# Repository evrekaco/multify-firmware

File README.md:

# multify-firmware
Sparkcore firmware resources for Multify

* Multify digital version android codes are available in digital_6wheels folder

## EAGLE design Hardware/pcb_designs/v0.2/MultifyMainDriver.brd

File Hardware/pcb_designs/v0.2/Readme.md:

Single sided version of the Multify main driver PCB.

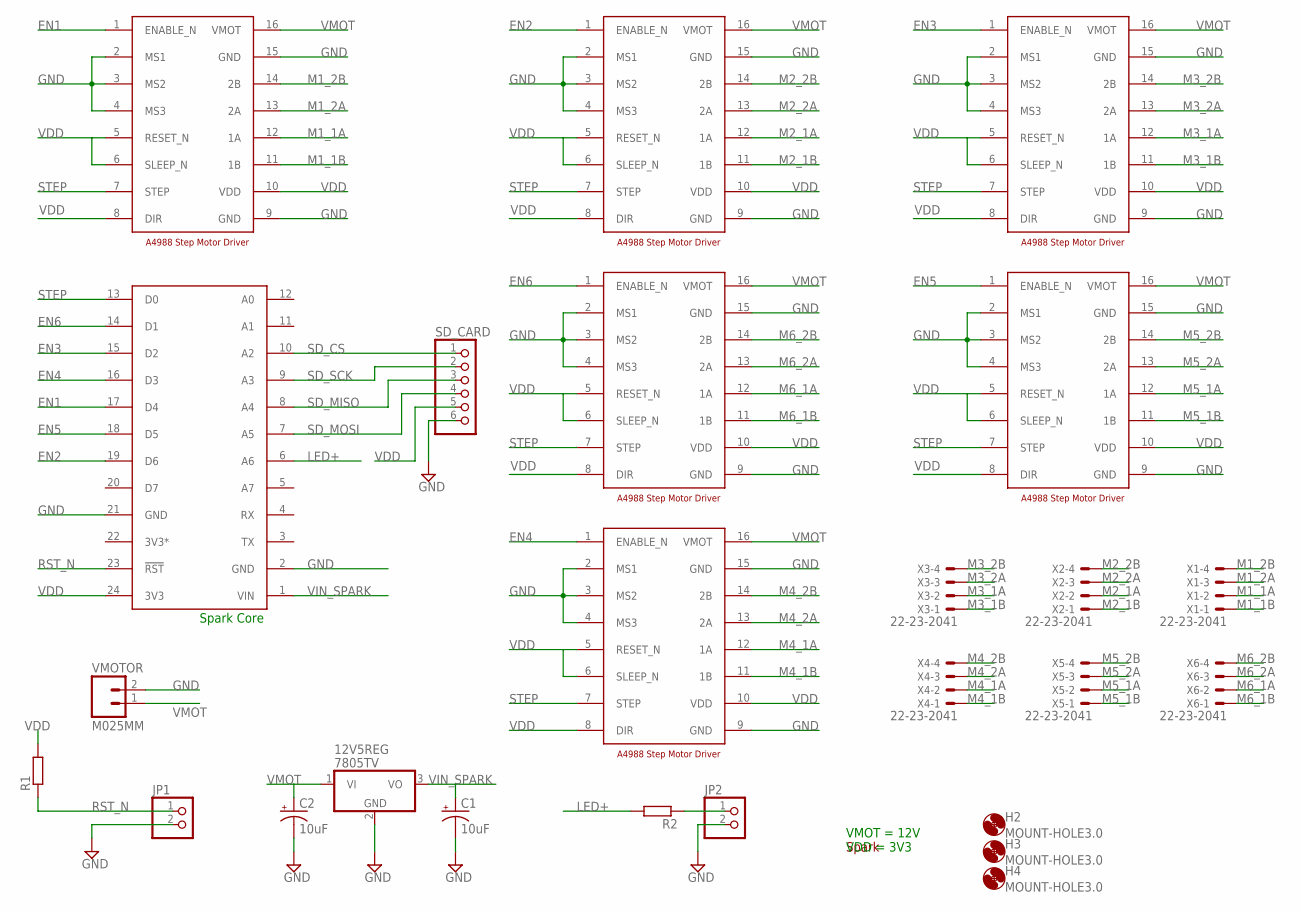
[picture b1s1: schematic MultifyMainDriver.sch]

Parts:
12V5REG: 7805TV; TO220V
C1, C2: 10uF; E3,5-8
DRIVER1, DRIVER2, DRIVER3, DRIVER4, DRIVER5, DRIVER6: A4988_DEV; A4988_PAC
H2, H3, H4: MOUNT-HOLE3.0; 3,0
JP1, JP2: PINHD-1X2; 1X02
R1, R2: R-EU_0207/7; 0207/7
SD_CARD: PINHD-1X6; 1X06
SPARK: SPARK_CORECORE; SPARK_CORE
U$2: SPARK_LOGO_WITH_PLANE; SPARK_LOGO_PLUS_PLANE
VMOTOR: M025MM; SCREWTERMINAL-5MM-2
X1, X2, X3, X4, X5, X6: 22-23-2041

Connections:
3V3*: SPARK.22 (3V3*)
EN1: DRIVER1.1 (ENABLE_N), SPARK.17 (D4)
EN2: DRIVER2.1 (ENABLE_N), SPARK.19 (D6)
EN3: DRIVER3.1 (ENABLE_N), SPARK.15 (D2)
EN4: DRIVER4.1 (ENABLE_N), SPARK.16 (D3)
EN5: DRIVER6.1 (ENABLE_N), SPARK.18 (D5)
EN6: DRIVER5.1 (ENABLE_N), SPARK.14 (D1)
GND: 12V5REG.2 (GND), C1.-, C2.-, DRIVER1.2 (MS1), DRIVER1.3 (MS2), DRIVER1.4 (MS3), DRIVER1.9 (GND), DRIVER1.15 (GND), DRIVER2.2 (MS1), DRIVER2.3 (MS2), DRIVER2.4 (MS3), DRIVER2.9 (GND), DRIVER2.15 (GND), DRIVER3.2 (MS1), DRIVER3.3 (MS2), DRIVER3.4 (MS3), DRIVER3.9 (GND), DRIVER3.15 (GND), DRIVER4.2 (MS1), DRIVER4.3 (MS2), DRIVER4.4 (MS3), DRIVER4.9 (GND), DRIVER4.15 (GND), DRIVER5.2 (MS1), DRIVER5.3 (MS2), DRIVER5.4 (MS3), DRIVER5.9 (GND), DRIVER5.15 (GND), DRIVER6.2 (MS1), DRIVER6.3 (MS2), DRIVER6.4 (MS3), DRIVER6.9 (GND), DRIVER6.15 (GND), JP1.2, JP2.2, SD_CARD.6, SPARK.2 (GND), SPARK.21 (GND), VMOTOR.2
LED+: R2.2, SPARK.6 (A6)
M1_1A: DRIVER1.12 (1A), X1.2
M1_1B: DRIVER1.11 (1B), X1.1
M1_2A: DRIVER1.13 (2A), X1.3
M1_2B: DRIVER1.14 (2B), X1.4
M2_1A: DRIVER2.12 (1A), X2.2
M2_1B: DRIVER2.11 (1B), X2.1
M2_2A: DRIVER2.13 (2A), X2.3
M2_2B: DRIVER2.14 (2B), X2.4
M3_1A: DRIVER3.12 (1A), X3.2
M3_1B: DRIVER3.11 (1B), X3.1
M3_2A: DRIVER3.13 (2A), X3.3
M3_2B: DRIVER3.14 (2B), X3.4
M4_1A: DRIVER4.12 (1A), X4.2
M4_1B: DRIVER4.11 (1B), X4.1
M4_2A: DRIVER4.13 (2A), X4.3
M4_2B: DRIVER4.14 (2B), X4.4
M5_1A: DRIVER6.12 (1A), X5.2
M5_1B: DRIVER6.11 (1B), X5.1
M5_2A: DRIVER6.13 (2A), X5.3
M5_2B: DRIVER6.14 (2B), X5.4
M6_1A: DRIVER5.12 (1A), X6.2
M6_1B: DRIVER5.11 (1B), X6.1
M6_2A: DRIVER5.13 (2A), X6.3
M6_2B: DRIVER5.14 (2B), X6.4
unnamed: JP2.1, R2.1
RST_N: JP1.1, R1.1, SPARK.23 (!RST)
SD_CS: SD_CARD.1, SPARK.10 (A2)
SD_MISO: SD_CARD.3, SPARK.8 (A4)
SD_MOSI: SD_CARD.4, SPARK.7 (A5)
SD_SCK: SD_CARD.2, SPARK.9 (A3)
STEP: DRIVER1.7 (STEP), DRIVER2.7 (STEP), DRIVER3.7 (STEP), DRIVER4.7 (STEP), DRIVER5.7 (STEP), DRIVER6.7 (STEP), SPARK.13 (D0)
VDD: DRIVER1.5 (RESET_N), DRIVER1.6 (SLEEP_N), DRIVER1.8 (DIR), DRIVER1.10 (VDD), DRIVER2.5 (RESET_N), DRIVER2.6 (SLEEP_N), DRIVER2.8 (DIR), DRIVER2.10 (VDD), DRIVER3.5 (RESET_N), DRIVER3.6 (SLEEP_N), DRIVER3.8 (DIR), DRIVER3.10 (VDD), DRIVER4.5 (RESET_N), DRIVER4.6 (SLEEP_N), DRIVER4.8 (DIR), DRIVER4.10 (VDD), DRIVER5.5 (RESET_N), DRIVER5.6 (SLEEP_N), DRIVER5.8 (DIR), DRIVER5.10 (VDD), DRIVER6.5 (RESET_N), DRIVER6.6 (SLEEP_N), DRIVER6.8 (DIR), DRIVER6.10 (VDD), R1.2, SD_CARD.5, SPARK.24 (3V3)
VIN_SPARK: 12V5REG.3 (VO), C1.+, SPARK.1 (VIN)
VMOT: 12V5REG.1 (VI), C2.+, DRIVER1.16 (VMOT), DRIVER2.16 (VMOT), DRIVER3.16 (VMOT), DRIVER4.16 (VMOT), DRIVER5.16 (VMOT), DRIVER6.16 (VMOT), VMOTOR.1

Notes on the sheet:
VMOT = 12V VDD = 3V3
Spark Core

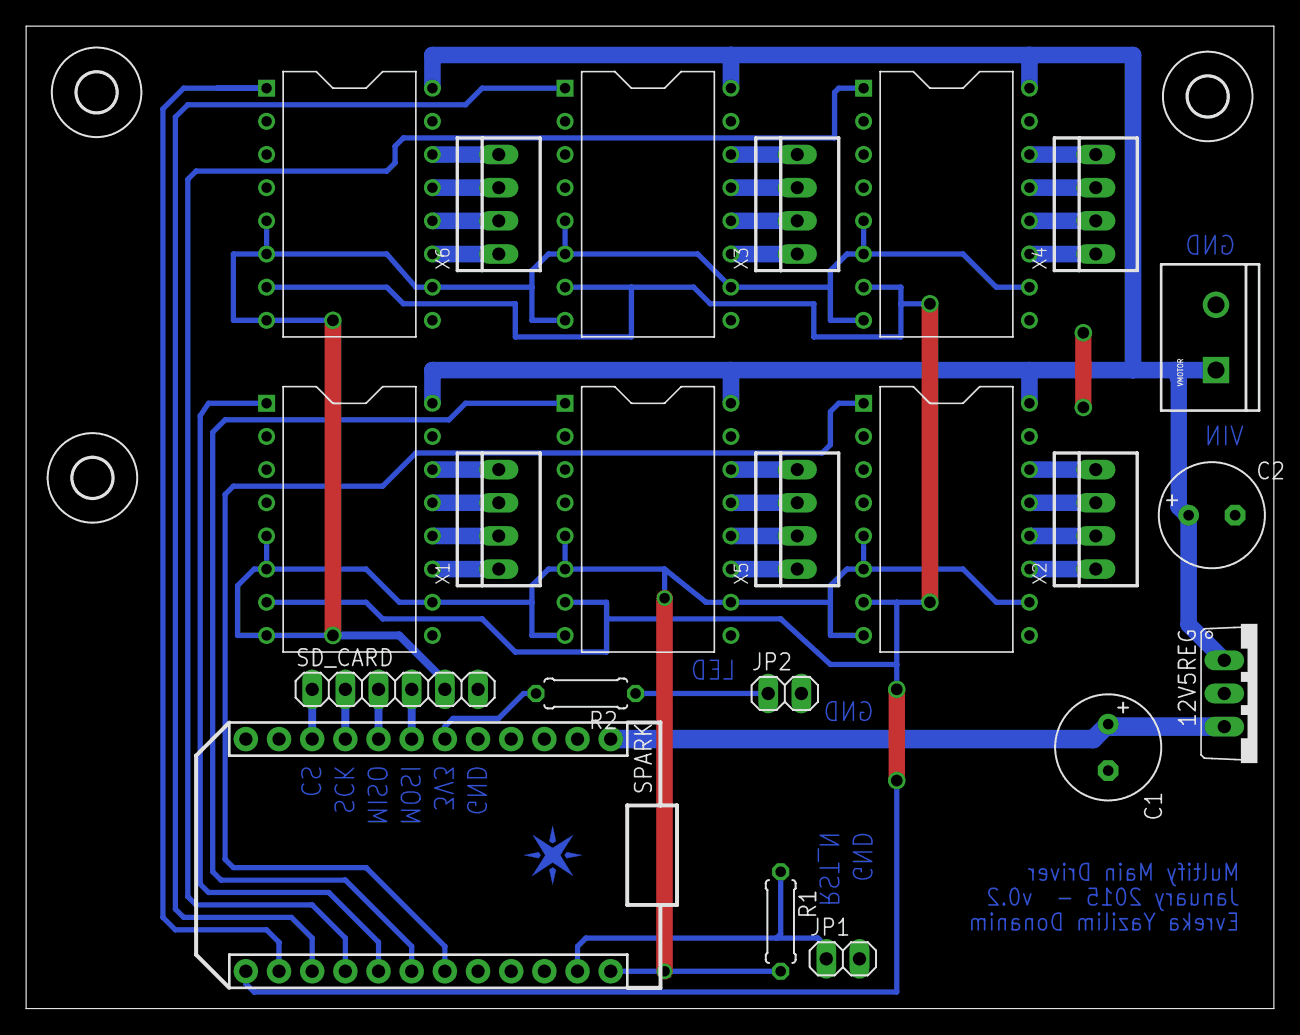
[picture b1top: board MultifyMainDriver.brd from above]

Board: 2 copper layers, 95.6 x 75.2 mm, 26 parts (1 on the bottom side), 42 nets.

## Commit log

2015-01-24 typo edit
2015-01-25 Create TCP_SDCard.ino
    TCP Request and SDCard Read Write functions together
2015-01-25 Create Http_SD_Changer
2015-01-25 Rename Http_SD_Changer to Http_SD_Changer.ino
2015-01-27 wrong http response bug is resolved
    before: at the begining, http request was not succesfully being received and therefore motors were turning unintentionally.
    after: spark waits for a succesful http response before comparing hard and server states
2015-01-27 Bug Fix and DEBUG Mode
    Bug fix of 'initial http response wait' implemented.
    Debug mode is implemented.
2015-01-27 Comments added
2015-01-28 Move motor bug fixed
2015-02-02 sdcard update
2015-02-04 Semi-automatic mode is activated
2015-02-10 reverse turn added
2015-02-10 positive turn bug fix
2015-02-13 SSID feature added
2015-02-19 auto ID, turn algorithm
    auto ID capture added, false turn algorith tested
2015-02-21 wifi overflow problem solved
2015-02-21 Update and rename parts to parts/test_code
2015-02-23 ssid text dosyası ismi değiştirildi
2015-02-23 turn algorithm updated
2015-03-13 moved to firmware
2015-03-13 updated with digital
2015-03-23 backend side is added
2015-04-05 Digital Ocean Server Updates
2015-04-08 '10 times turn' is ommitted
2015-04-15 firmware and hardware is merged
2015-04-15 düzenleme
2015-04-15 old version web sitesi added
2015-04-22 User Manual Eng added
2015-04-22 eng version added
2015-05-13 Move_all function added
2015-05-13 quick start guide translated

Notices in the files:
parts and their libraries:
SparkFun-Connectors: Licensing: Creative Commons ShareAlike 4.0 International - https://creativecommons.org/licenses/by-sa/4.0
